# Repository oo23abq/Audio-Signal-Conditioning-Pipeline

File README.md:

# Precision, Analogue Signal Conditioning Board for ADC Aquisition

**Overview**
* This project implements a complete analogue front-end (AFE) for conditioning audio/sensor signals before digitisation by an AD4695 high‑resolution ADC.
* Simulated and verified in LTspice & designed in KICAD.

The system includes:

* A preamp stage
* A high‑pass filter (HPF)
* A low‑pass filter (LPF)
* A precision VMID bias network
* A fully‑differential ADC driver
* A 3.3 V LDO rail
* ±12 V analog supply rails
* Full hierarchical KiCad schematic design
* LTspice simulation of all analogue blocks

In total, the design uses 36 caps, 33 resistors, 2 silicon diodes, 3 connectors, 15 test points and a selection of 10 ICs. 
*  Total = 99 components  
* The six opamps used were all ADA4084‑2 dual models, chosen for their low noise, high BW, and excellent linearity.

This repository documents the entire engineering workflow, including schematic design, simulation, PCB layout, testing, and future improvements.

System Architecture
  *The signal chain is structured as follows -->
  
1) Preamp Stage
    * Differential microphone/sensor input
    * RF/ESD protection
    * Gain + impedance matching

2) High‑Pass Filter (HPF)
    * Removes DC offset
    * Sets lower cutoff (~15–20 Hz depending on configuration)
    * Biased at VMID

3) Low‑Pass Filter (LPF)
    * Sallen‑Key topology
    * Sets upper cutoff (~15–20 kHz)
    * Unity gain
    * Biased at VMID

4) ADC Driver
    * Fully differential
    * Sets ADC common‑mode
    * Drives AD4695 input stage

5) ADC Interface
    * Reference (4.096 V)
    * LDO (3.3 V)
    * Digital interface pins

6) Power Rails
    * ±12 V analogue rails
    * 3.3 V LDO
    * VMID bias generator
    * Reference buffer

Key Features
  * Hierarchical KiCad design with clean sheet‑to‑sheet signal flow
  * Zero ERC errors (verified)
  * Proper VMID/GND separation
  * Full LTspice simulation of each stage
  * Modular archiecture for easy reuse

Fabricated by JLCPCB.

## Repository Structure

```markdown

```text
├── docs/                                       # General Documentation  
│   └── report/                                 
│       └── sig_conditioning_board_report.docx  # Lab Test Report 
├── gerbers/                                    # Manufacturing Files
│   └── audioafegerbers.zip                     # Production Gerber and drill archives
├── images/                                     # 3D Renders 
│   └── pcb/                                    
│       └── 3dpcb.png                           # Assembled Board 
├── kicad/                                      # Complete KiCad hardware project
│   ├── schematics/                             # Hierarchical Schematics
│   │   ├── signal_conditioning_top.kicad_sch   # Top Level 
│   │   ├── conditioning_input.kicad_sch        # Input Stage
│   │   ├── conditioning_preamp.kicad_sch       # Preamplifier 
│   │   ├── conditioning_highpass.kicad_sch     # High-Pass Filter
│   │   ├── conditioning_lowpass.kicad_sch      # Low-Pass Filter
│   │   ├── conditioning_driver.kicad_sch       # ADC Driver / Buffer
│   │   ├── conditioning_adc.kicad_sch          # ADC Interface
│   │   ├── conditioning_power.kicad_sch        # Power / Rails 
│   │   └── conditioning_testpoints.kicad_sch   # Test Points
│   ├── signal_conditioning_top.kicad_pcb       # PCB Board File 
│   └── signal_conditioning_bom.csv             # Bill of Materials
├── ltspice/                                    # Analogue Simulation 
│   └── waveform.png                            # Transient / Hz Response Plots 
├── LICENSE                                     # MIT License File
└── README.md                                   # Project Guidance / Info

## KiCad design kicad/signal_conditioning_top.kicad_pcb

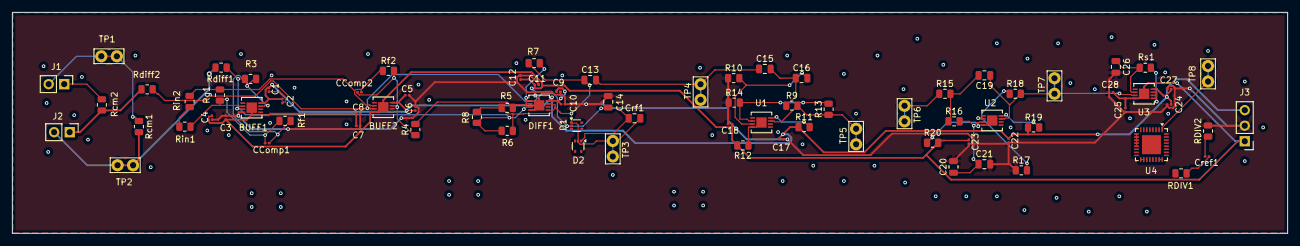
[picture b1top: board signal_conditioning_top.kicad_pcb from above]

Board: 2 copper layers, 208.3 x 36.1 mm, 82 parts (0 on the bottom side), 39 nets.

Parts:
BUFF1, BUFF2: ADA4084-2ACPZ-R7; CP_8_12_ADI
C1, C4, C5, C8, C9, C12, C17, C18, C22, C23, C24, C28: 100n; C_0201_0603Metric
C2, C3, C6, C7, C10, C11, C25, C27: 10u; C_0201_0603Metric
C13, C14: 220p; C_0805_2012Metric
C15, C16: 220n; C_0805_2012Metric
C19: 820p; C_0805_2012Metric
C20: 680p; C_0805_2012Metric
C21: 150p; C_0805_2012Metric
C26: 50n; C_0805_2012Metric
CComp1, CComp2: 10p; C_0201_0603Metric
Cref1: 4.7u; C_0201_0603Metric
Crf1: 100p; C_0805_2012Metric
D1, D2: BAV99; Diodes_SOT-553
DIFF1: ADA4084-2ACPZ-R7; CP_8_12_ADI
J1: VCM; PinHeader_1x02_P2.54mm_Vertical
J2: VMIC; PinHeader_1x02_P2.54mm_Vertical
J3: Conn_01x03; PinHeader_1x03_P2.54mm_Vertical
R3, R4, R5, R6, R7, R8, R13, R14, R15, R16, R17, R18: 10k; R_0805_2012Metric
R9, R10: 27k; R_0805_2012Metric
R11, R12, R19, R20: 10; R_0805_2012Metric
RDIV1, RDIV2: 10k; R_0805_2012Metric
Rcm1, Rcm2: 100; R_0805_2012Metric
Rdiff1, Rdiff2: 100; R_0805_2012Metric
Rf1, Rf2: 24.9k; R_0805_2012Metric
Rg1: 499; R_0805_2012Metric
Rin1, Rin2: 24.9k; R_0805_2012Metric
Rs1: 50; R_0805_2012Metric
TP1, TP2, TP3, TP8: TestPoint; TestPoint_Bridge_Pitch2.54mm_Drill1.0mm
TP4, TP5, TP6, TP7: TestPoint_Bridge_Pitch2.54mm_Drill1.0mm
U1, U2, U3: ADA4084-2ACPZ-R7; CP_8_12_ADI
U4: AD4695; LFCSP-32-1EP_5x5mm_P0.5mm_EP3.1x3.1mm

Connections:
/ADC Driver/ADC_IN: C26.1, Rs1.2, U3.2 (INA-)
/ADC Driver/LP_OUT: C19.1, R18.2, TP7.1, U2.7 (OUTB), U3.3 (INA+)
/ADC Interface/LP_OUT: TP8.1, U4.1 (IN0)
/HPF/HP_IN: C13.2, C15.1, TP4.1
/HPF/HP_OUT: R9.2, R13.1, TP5.1, U1.7 (OUTB)
/LPF/HP_OUT: R15.1, TP6.1
AGND: BUFF1.4 (V-), C3.1, C4.1, C5.2, C6.2, C7.2, C8.2, C9.1, C10.1, C11.2, C12.2, C14.2, C17.2, C18.2, C20.2, C21.2, C22.2, C23.2, C24.2, C25.2, C26.2, C27.2, C28.2, J3.2, R10.1, R14.1, R17.1, RDIV2.2
CM+: J1.2, Rcm1.1, TP1.1
CM-: J1.1, Rcm2.1
GND: Cref1.1, RDIV1.2
MIC+: J2.2, Rcm1.2, Rdiff1.1, TP2.1
MIC-: J2.1, Rcm2.2, Rdiff2.1
MICRF+: C13.1, Crf1.2, D1.1, D2.2, DIFF1.7 (OUTB), R5.2, R6.2, R7.2, R8.2, TP3.1
MICRF-: BUFF2.3 (INA+), C14.1, Crf1.1, D1.2, D2.1, Rdiff2.2
unnamed: BUFF1.3 (INA+), DIFF1.3 (INA+), R3.2, R6.1, R8.1, Rdiff1.2
unnamed: BUFF1.2 (INA-), CComp1.1, Rf1.1, Rg1.1, Rin1.2
unnamed: BUFF1.7 (OUTB), CComp1.2, R3.1, Rf1.2
unnamed: BUFF2.2 (INA-), CComp2.1, Rf2.1, Rg1.2, Rin2.1
unnamed: BUFF2.7 (OUTB), CComp2.2, R4.1, Rf2.2
unnamed: C1.2, C2.2
unnamed: C15.2, C16.1, R9.1
unnamed: C19.2, R15.2, R16.1
unnamed: Cref1.2, RDIV2.1
unnamed: DIFF1.2 (INA-), R4.2, R5.1, R7.1
unnamed: Rin1.1, Rin2.2
unnamed: R12.1, U1.4 (V-), U1.HTAB (EPAD)
unnamed: C16.2, R10.2, U1.3 (INA+)
unnamed: R13.2, R14.2, U1.2 (INA-)
unnamed: R11.2, U1.8 (V+)
unnamed: R20.1, U2.4 (V-), U2.HTAB (EPAD)
unnamed: C20.1, C21.1, R16.2, U2.3 (INA+)
unnamed: R17.2, R18.1, U2.2 (INA-)
unnamed: R19.2, U2.8 (V+)
unnamed: Rs1.1, U3.7 (OUTB)
unnamed: U4.17 (VSAMPLE), U4.18 (RESET)
REF: U4.23 (REF), U4.24 (REFIN)
REFGND: U4.9 (COMM), U4.10 (SLCT0), U4.11 (SLCT1), U4.12 (SLCT2), U4.13 (REFGND)
V+: BUFF1.8 (V+), BUFF2.8 (V+), C1.1, C2.1, C5.1, C6.1, C9.2, C10.2, C17.1, C22.1, C24.1, C27.1, DIFF1.8 (V+), J3.3, R11.1, R19.1, U3.8 (V+)
V-: BUFF1.HTAB (EPAD), BUFF2.4 (V-), BUFF2.HTAB (EPAD), C3.2, C4.2, C7.1, C8.1, C11.1, C12.1, C18.1, C23.1, C25.1, C28.1, DIFF1.4 (V-), DIFF1.HTAB (EPAD), J3.1, R12.2, R20.2, U3.4 (V-), U3.HTAB (EPAD)

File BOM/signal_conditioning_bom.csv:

Reference,Value,Footprint,Datasheet,Description
BUFF1,ADA4084-2,Package_SO:SOIC-8_5.3x5.3mm_P1.27mm,,
BUFF2,ADA4084-2,Package_SO:SOIC-8_5.3x5.3mm_P1.27mm,,
C1,100n,Capacitor_SMD:C_0201_0603Metric,~,Unpolarized capacitor
C2,10u,Capacitor_SMD:C_0201_0603Metric,~,Unpolarized capacitor
C3,10u,Capacitor_SMD:C_0201_0603Metric,~,Unpolarized capacitor
C4,100n,Capacitor_SMD:C_0201_0603Metric,~,Unpolarized capacitor
C5,100n,Capacitor_SMD:C_0201_0603Metric,~,Unpolarized capacitor
C6,10u,Capacitor_SMD:C_0201_0603Metric,~,Unpolarized capacitor
C7,10u,Capacitor_SMD:C_0201_0603Metric,~,Unpolarized capacitor
C8,100n,Capacitor_SMD:C_0201_0603Metric,~,Unpolarized capacitor
C9,100n,Capacitor_SMD:C_0201_0603Metric,~,Unpolarized capacitor
C10,10u,Capacitor_SMD:C_0201_0603Metric,~,Unpolarized capacitor
C11,10u,Capacitor_SMD:C_0201_0603Metric,~,Unpolarized capacitor
C12,100n,Capacitor_SMD:C_0201_0603Metric,~,Unpolarized capacitor
C13,220p,Capacitor_SMD:C_0805_2012Metric,~,Unpolarized capacitor
C14,220p,Capacitor_SMD:C_0805_2012Metric,~,Unpolarized capacitor
C15,220n,Capacitor_SMD:C_0805_2012Metric,~,Unpolarized capacitor
C16,220n,Capacitor_SMD:C_0805_2012Metric,~,Unpolarized capacitor
C17,100n,Capacitor_SMD:C_0201_0603Metric,~,Unpolarized capacitor
C18,100n,Capacitor_SMD:C_0201_0603Metric,~,Unpolarized capacitor
C19,820p,Capacitor_SMD:C_0805_2012Metric,~,Unpolarized capacitor
C20,680p,Capacitor_SMD:C_0805_2012Metric,~,Unpolarized capacitor
C21,150p,Capacitor_SMD:C_0805_2012Metric,~,Unpolarized capacitor
C22,100n,Capacitor_SMD:C_0201_0603Metric,~,Unpolarized capacitor
C23,100n,Capacitor_SMD:C_0201_0603Metric,~,Unpolarized capacitor
C24,100n,Capacitor_SMD:C_0201_0603Metric,~,Unpolarized capacitor
C25,10u,Capacitor_SMD:C_0201_0603Metric,~,Unpolarized capacitor
C26,50n,Capacitor_SMD:C_0805_2012Metric,~,Unpolarized capacitor
C27,10u,Capacitor_SMD:C_0201_0603Metric,~,Unpolarized capacitor
C28,100n,Capacitor_SMD:C_0201_0603Metric,~,Unpolarized capacitor
CComp1,10p,Capacitor_SMD:C_0201_0603Metric,~,Unpolarized capacitor
CComp2,10p,Capacitor_SMD:C_0201_0603Metric,~,Unpolarized capacitor
Cref1,4.7u,Capacitor_SMD:C_0201_0603Metric,~,Unpolarized capacitor
Crf1,100p,Capacitor_SMD:C_0805_2012Metric,~,Unpolarized capacitor
D1,BAV99,Package_TO_SOT_SMD:Diodes_SOT-553,,
D2,BAV99,Package_TO_SOT_SMD:Diodes_SOT-553,,
DIFF1,ADA4084-2,Package_SO:SOIC-8_5.3x5.3mm_P1.27mm,,
J1,VCM,Connector_PinHeader_2.54mm:PinHeader_1x02_P2.54mm_Vertical,~,"Generic connector, single row, 01x02, script generated (kicad-library-utils/schlib/autogen/connector/)"
J2,VMIC,Connector_PinHeader_2.54mm:PinHeader_1x02_P2.54mm_Vertical,~,"Generic connector, single row, 01x02, script generated (kicad-library-utils/schlib/autogen/connector/)"
J3,Conn_01x03,Connector_PinHeader_2.54mm:PinHeader_1x03_P2.54mm_Vertical,~,"Generic connector, single row, 01x03, script generated (kicad-library-utils/schlib/autogen/connector/)"
R3,10k,Resistor_SMD:R_0805_2012Metric,~,"Resistor, US symbol"
R4,10k,Resistor_SMD:R_0805_2012Metric,~,"Resistor, US symbol"
R5,10k,Resistor_SMD:R_0805_2012Metric,~,"Resistor, US symbol"
R6,10k,Resistor_SMD:R_0805_2012Metric,~,"Resistor, US symbol"
R7,10k,Resistor_SMD:R_0805_2012Metric,~,"Resistor, US symbol"
R8,10k,Resistor_SMD:R_0805_2012Metric,~,"Resistor, US symbol"
R9,27k,Resistor_SMD:R_0805_2012Metric,~,"Resistor, US symbol"
R10,27k,Resistor_SMD:R_0805_2012Metric,~,"Resistor, US symbol"
R11,10,Resistor_SMD:R_0805_2012Metric,~,"Resistor, US symbol"
R12,10,Resistor_SMD:R_0805_2012Metric,~,"Resistor, US symbol"
R13,10k,Resistor_SMD:R_0805_2012Metric,~,"Resistor, US symbol"
R14,10k,Resistor_SMD:R_0805_2012Metric,~,"Resistor, US symbol"
R15,10k,Resistor_SMD:R_0805_2012Metric,~,"Resistor, US symbol"
R16,10k,Resistor_SMD:R_0805_2012Metric,~,"Resistor, US symbol"
R17,10k,Resistor_SMD:R_0805_2012Metric,~,"Resistor, US symbol"
R18,10k,Resistor_SMD:R_0805_2012Metric,~,"Resistor, US symbol"
R19,10,Resistor_SMD:R_0805_2012Metric,~,"Resistor, US symbol"
R20,10,Resistor_SMD:R_0805_2012Metric,~,"Resistor, US symbol"
Rcm1,100,Resistor_SMD:R_0805_2012Metric,~,"Resistor, US symbol"
Rcm2,100,Resistor_SMD:R_0805_2012Metric,~,"Resistor, US symbol"
Rdiff1,100,Resistor_SMD:R_0805_2012Metric,~,"Resistor, US symbol"
Rdiff2,100,Resistor_SMD:R_0805_2012Metric,~,"Resistor, US symbol"
RDIV1,10k,Resistor_SMD:R_0805_2012Metric,~,"Resistor, US symbol"
RDIV2,10k,Resistor_SMD:R_0805_2012Metric,~,"Resistor, US symbol"
Rf1,24.9k,Resistor_SMD:R_0805_2012Metric,~,"Resistor, US symbol"
Rf2,24.9k,Resistor_SMD:R_0805_2012Metric,~,"Resistor, US symbol"
Rg1,499,Resistor_SMD:R_0805_2012Metric,~,"Resistor, US symbol"
Rin1,24.9k,Resistor_SMD:R_0805_2012Metric,~,"Resistor, US symbol"
Rin2,24.9k,Resistor_SMD:R_0805_2012Metric,~,"Resistor, US symbol"
Rs1,50,Resistor_SMD:R_0805_2012Metric,~,"Resistor, US symbol"
TestPoint1,TestPoint,,~,test point
TestPoint2,TestPoint,,~,test point
TestPoint3,TestPoint,,~,test point
TestPoint4,TestPoint,,~,test point
TestPoint5,TestPoint,,~,test point
TestPoint6,TestPoint,,~,test point
TestPoint7,TestPoint,,~,test point
TP1,TestPoint,TestPoint:TestPoint_Bridge_Pitch2.54mm_Drill1.0mm,~,test point
TP2,TestPoint,TestPoint:TestPoint_Bridge_Pitch2.54mm_Drill1.0mm,~,test point
TP3,TestPoint,TestPoint:TestPoint_Bridge_Pitch2.54mm_Drill1.0mm,~,test point
TP4,TestPoint,TestPoint:TestPoint_Bridge_Pitch2.54mm_Drill1.0mm,~,test point
TP5,TestPoint,TestPoint:TestPoint_Bridge_Pitch2.54mm_Drill1.0mm,~,test point
TP6,~,TestPoint:TestPoint_Bridge_Pitch2.54mm_Drill1.0mm,~,test point
TP7,~,TestPoint:TestPoint_Bridge_Pitch2.54mm_Drill1.0mm,~,test point
TP8,TestPoint,TestPoint:TestPoint_Bridge_Pitch2.54mm_Drill1.0mm,~,test point
U1,ADA4084-2,Package_SO:SOIC-8_5.3x5.3mm_P1.27mm,,
U4,ADA4084-2,Package_SO:SOIC-8_5.3x5.3mm_P1.27mm,,
U6,ADA4084-2,Package_SO:SOIC-8_5.3x5.3mm_P1.27mm,,
U11,AD4695,Package_CSP:LFCSP-32-1EP_5x5mm_P0.5mm_EP3.1x3.1mm,,
V-2,3.3,,,
V4,3.3,,,
V7,3.3,,,
V12,12,,,
V17,-12,,,
VCNV2,3.3,,,
VLDO2,3.3,,,
VREF2,4.096,,,
